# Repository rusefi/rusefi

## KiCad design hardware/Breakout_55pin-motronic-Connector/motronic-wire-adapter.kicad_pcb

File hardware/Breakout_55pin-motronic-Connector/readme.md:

This version of the 55 pin seems to be used by Bosch on BMW/GM ECUs around 1.5.x

See [here](../Breakout_55pin_963063-15-Connector) for another version of connector

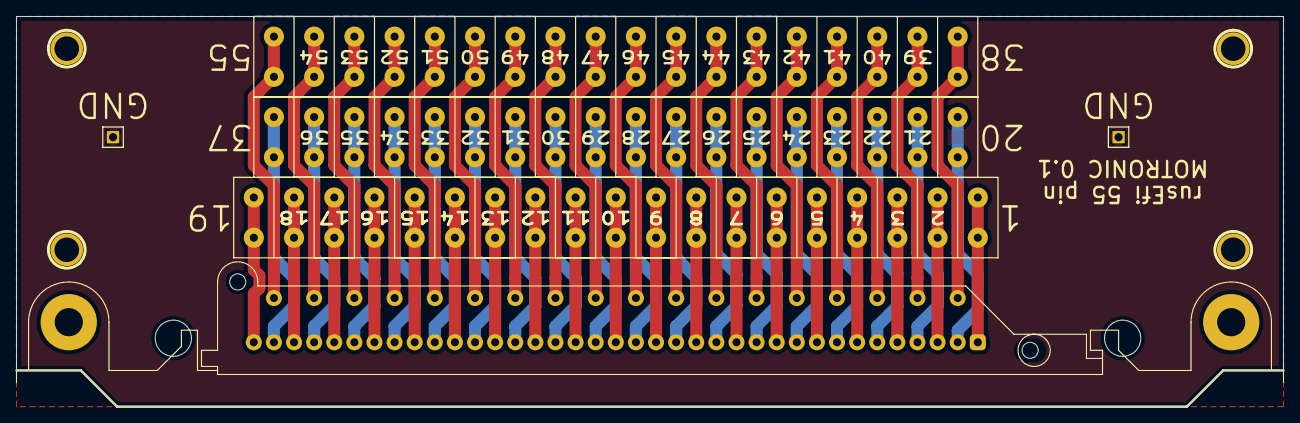
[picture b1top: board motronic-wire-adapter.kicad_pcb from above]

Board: 2 copper layers, 157.5 x 48.5 mm, 10 parts (0 on the bottom side), 56 nets.

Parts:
1PIN, 1PIN#2, 1PIN#3, 1PIN#4: P***; 1pin
P1: MOTRONIC; 55pin_china_bosch_motronic
P2: CONN_19; CON19X5
P3, P4: CONN_18; CON18X5
P5, P6: CONN_1; PIN_ARRAY_1

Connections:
GND: P5.1, P6.1
unnamed: P1.11, P2.11
unnamed: P1.1, P2.1
unnamed: P1.2, P2.2
unnamed: P1.3, P2.3
unnamed: P1.4, P2.4
unnamed: P1.5, P2.5
unnamed: P1.6, P2.6
unnamed: P1.7, P2.7
unnamed: P1.8, P2.8
unnamed: P1.9, P2.9
unnamed: P1.10, P2.10
unnamed: P1.55, P4.18
unnamed: P1.12, P2.12
unnamed: P1.13, P2.13
unnamed: P1.14, P2.14
unnamed: P1.15, P2.15
unnamed: P1.16, P2.16
unnamed: P1.17, P2.17
unnamed: P1.18, P2.18
unnamed: P1.19, P2.19
unnamed: P1.20, P3.1
unnamed: P1.21, P3.2
unnamed: P1.44, P4.7
unnamed: P1.34, P3.15
unnamed: P1.35, P3.16
unnamed: P1.36, P3.17
unnamed: P1.37, P3.18
unnamed: P1.38, P4.1
unnamed: P1.39, P4.2
unnamed: P1.40, P4.3
unnamed: P1.41, P4.4
unnamed: P1.42, P4.5
unnamed: P1.43, P4.6
unnamed: P1.22, P3.3
unnamed: P1.45, P4.8
unnamed: P1.46, P4.9
unnamed: P1.47, P4.10
unnamed: P1.48, P4.11
unnamed: P1.49, P4.12
unnamed: P1.50, P4.13
unnamed: P1.51, P4.14
unnamed: P1.52, P4.15
unnamed: P1.53, P4.16
unnamed: P1.54, P4.17
unnamed: P1.33, P3.14
unnamed: P1.23, P3.4
unnamed: P1.24, P3.5
unnamed: P1.25, P3.6
unnamed: P1.26, P3.7
unnamed: P1.27, P3.8
unnamed: P1.28, P3.9
unnamed: P1.29, P3.10
unnamed: P1.30, P3.11
unnamed: P1.31, P3.12
unnamed: P1.32, P3.13

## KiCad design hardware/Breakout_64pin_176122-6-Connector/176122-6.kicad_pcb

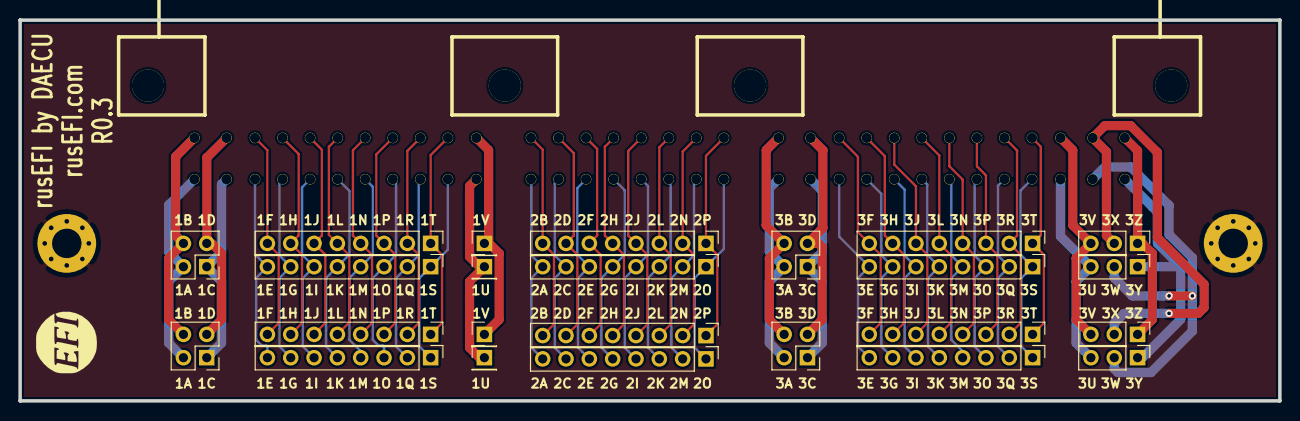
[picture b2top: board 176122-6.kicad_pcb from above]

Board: 2 copper layers, 137.2 x 41.5 mm, 28 parts (0 on the bottom side), 65 nets.

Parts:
G1: LOGO
H1, H2: MountingHole_Pad; MountingHole_3.2mm_M3_Pad_Via
P1, P2, P13, P14: CONN_3; PinHeader_1x03_P2.54mm_Vertical
P3, P4, P42, P43: Conn_01x04_Male; PinHeader_2x02_P2.54mm_Vertical
P7, P8, P19, P20: CONN_1; PinHeader_1x01_P2.54mm_Vertical
P25: 0176122-06; 176122-6
P26, P27, P28, P29, P30, P31, P32, P33, P34, P35, P36, P37: CONN_8; PinHeader_1x08_P2.54mm_Vertical

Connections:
GND: H1.1, H2.1
unnamed: P1.1, P13.1, P25.1
unnamed: P1.2, P13.2, P25.2
unnamed: P1.3, P13.3, P25.3
unnamed: P2.1, P14.1, P25.4
unnamed: P2.2, P14.2, P25.5
unnamed: P2.3, P14.3, P25.6
unnamed: P7.1, P19.1, P25.11
unnamed: P8.1, P20.1, P25.12
unnamed: P3.1, P4.1, P25.7
unnamed: P3.2, P4.2, P25.8
unnamed: P3.3, P4.3, P25.9
unnamed: P3.4, P4.4, P25.10
unnamed: P25.13, P42.1, P43.1
unnamed: P25.14, P42.2, P43.2
unnamed: P25.15, P42.3, P43.3
unnamed: P25.16, P42.4, P43.4
unnamed: P25.17, P26.1, P32.1
unnamed: P25.18, P26.2, P32.2
unnamed: P25.19, P26.3, P32.3
unnamed: P25.20, P26.4, P32.4
unnamed: P25.21, P26.5, P32.5
unnamed: P25.22, P26.6, P32.6
unnamed: P25.23, P26.7, P32.7
unnamed: P25.24, P26.8, P32.8
unnamed: P25.25, P27.1, P33.1
unnamed: P25.26, P27.2, P33.2
unnamed: P25.27, P27.3, P33.3
unnamed: P25.28, P27.4, P33.4
unnamed: P25.29, P27.5, P33.5
unnamed: P25.30, P27.6, P33.6
unnamed: P25.31, P27.7, P33.7
unnamed: P25.32, P27.8, P33.8
unnamed: P25.33, P28.1, P34.1
unnamed: P25.34, P28.2, P34.2
unnamed: P25.35, P28.3, P34.3
unnamed: P25.36, P28.4, P34.4
unnamed: P25.37, P28.5, P34.5
unnamed: P25.38, P28.6, P34.6
unnamed: P25.39, P28.7, P34.7
unnamed: P25.40, P28.8, P34.8
unnamed: P25.41, P29.1, P35.1
unnamed: P25.42, P29.2, P35.2
unnamed: P25.43, P29.3, P35.3
unnamed: P25.44, P29.4, P35.4
unnamed: P25.45, P29.5, P35.5
unnamed: P25.46, P29.6, P35.6
unnamed: P25.47, P29.7, P35.7
unnamed: P25.48, P29.8, P35.8
unnamed: P25.49, P30.1, P36.1
unnamed: P25.50, P30.2, P36.2
unnamed: P25.51, P30.3, P36.3
unnamed: P25.52, P30.4, P36.4
unnamed: P25.53, P30.5, P36.5
unnamed: P25.54, P30.6, P36.6
unnamed: P25.55, P30.7, P36.7
unnamed: P25.56, P30.8, P36.8
unnamed: P25.57, P31.1, P37.1
unnamed: P25.58, P31.2, P37.2
unnamed: P25.59, P31.3, P37.3
unnamed: P25.60, P31.4, P37.4
unnamed: P25.61, P31.5, P37.5
unnamed: P25.62, P31.6, P37.6
unnamed: P25.63, P31.7, P37.7
unnamed: P25.64, P31.8, P37.8

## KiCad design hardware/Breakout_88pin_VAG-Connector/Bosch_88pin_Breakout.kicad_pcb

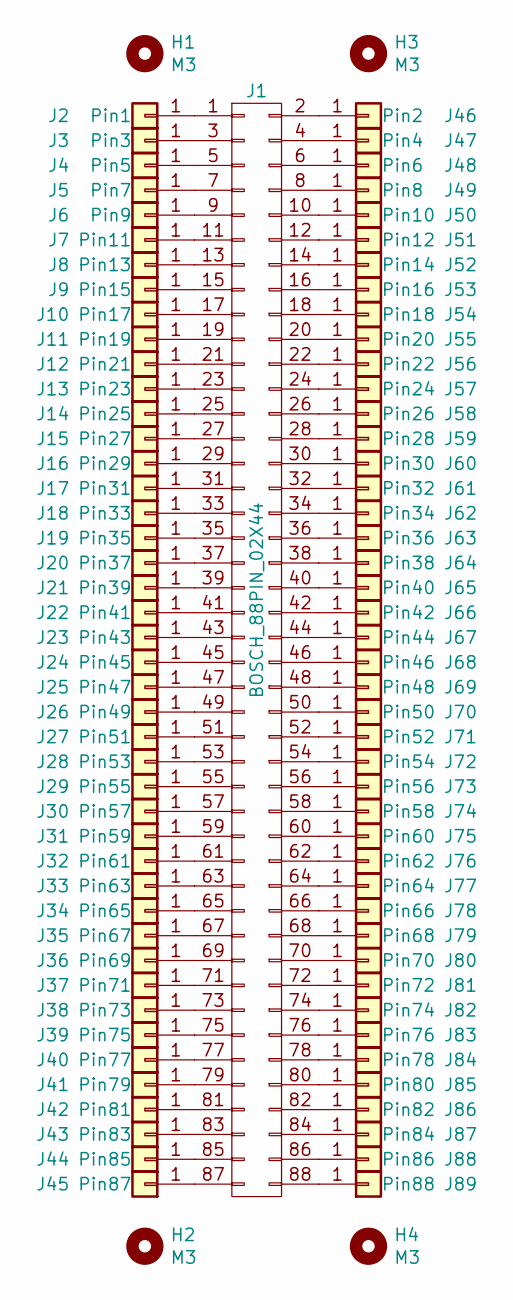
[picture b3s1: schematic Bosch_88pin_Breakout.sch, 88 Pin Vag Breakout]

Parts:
H1, H2, H3, H4: M3; MountingHole_3.2mm_M3_DIN965
J1: BOSCH_88PIN_02X44; BOSCH-88pin
J2: Pin1; TestPoint_Bridge_Pitch2.54mm_Drill1.3mm
J3: Pin3; TestPoint_Bridge_Pitch2.54mm_Drill1.3mm
J4: Pin5; TestPoint_Bridge_Pitch2.54mm_Drill1.3mm
J5: Pin7; TestPoint_Bridge_Pitch2.54mm_Drill1.3mm
J6: Pin9; TestPoint_Bridge_Pitch2.54mm_Drill1.3mm
J7: Pin11; TestPoint_Bridge_Pitch2.54mm_Drill1.3mm
J8: Pin13; TestPoint_Bridge_Pitch2.54mm_Drill1.3mm
J9: Pin15; TestPoint_Bridge_Pitch2.54mm_Drill1.3mm
J10: Pin17; TestPoint_Bridge_Pitch2.54mm_Drill1.3mm
J11: Pin19; TestPoint_Bridge_Pitch2.54mm_Drill1.3mm
J12: Pin21; TestPoint_Bridge_Pitch2.54mm_Drill1.3mm
J13: Pin23; TestPoint_Bridge_Pitch2.54mm_Drill1.3mm
J14: Pin25; TestPoint_Bridge_Pitch2.54mm_Drill1.3mm
J15: Pin27; TestPoint_Bridge_Pitch2.54mm_Drill1.3mm
J16: Pin29; TestPoint_Bridge_Pitch2.54mm_Drill1.3mm
J17: Pin31; TestPoint_Bridge_Pitch2.54mm_Drill1.3mm
J18: Pin33; TestPoint_Bridge_Pitch2.54mm_Drill1.3mm
J19: Pin35; TestPoint_Bridge_Pitch2.54mm_Drill1.3mm
J20: Pin37; TestPoint_Bridge_Pitch2.54mm_Drill1.3mm
J21: Pin39; TestPoint_Bridge_Pitch2.54mm_Drill1.3mm
J22: Pin41; TestPoint_Bridge_Pitch2.54mm_Drill1.3mm
J23: Pin43; TestPoint_Bridge_Pitch2.54mm_Drill1.3mm
J24: Pin45; TestPoint_Bridge_Pitch2.54mm_Drill1.3mm
J25: Pin47; TestPoint_Bridge_Pitch2.54mm_Drill1.3mm
J26: Pin49; TestPoint_Bridge_Pitch2.54mm_Drill1.3mm
J27: Pin51; TestPoint_Bridge_Pitch2.54mm_Drill1.3mm
J28: Pin53; TestPoint_Bridge_Pitch2.54mm_Drill1.3mm
J29: Pin55; TestPoint_Bridge_Pitch2.54mm_Drill1.3mm
J30: Pin57; TestPoint_Bridge_Pitch2.54mm_Drill1.3mm
J31: Pin59; TestPoint_Bridge_Pitch2.54mm_Drill1.3mm
J32: Pin61; TestPoint_Bridge_Pitch2.54mm_Drill1.3mm
J33: Pin63; TestPoint_Bridge_Pitch2.54mm_Drill1.3mm
J34: Pin65; TestPoint_Bridge_Pitch2.54mm_Drill1.3mm
J35: Pin67; TestPoint_Bridge_Pitch2.54mm_Drill1.3mm
J36: Pin69; TestPoint_Bridge_Pitch2.54mm_Drill1.3mm
J37: Pin71; TestPoint_Bridge_Pitch2.54mm_Drill1.3mm
J38: Pin73; TestPoint_Bridge_Pitch2.54mm_Drill1.3mm
J39: Pin75; TestPoint_Bridge_Pitch2.54mm_Drill1.3mm
J40: Pin77; TestPoint_Bridge_Pitch2.54mm_Drill1.3mm
J41: Pin79; TestPoint_Bridge_Pitch2.54mm_Drill1.3mm
J42: Pin81; TestPoint_Bridge_Pitch2.54mm_Drill1.3mm
J43: Pin83; TestPoint_Bridge_Pitch2.54mm_Drill1.3mm
J44: Pin85; TestPoint_Bridge_Pitch2.54mm_Drill1.3mm
J45: Pin87; TestPoint_Bridge_Pitch2.54mm_Drill1.3mm
J46: Pin2; TestPoint_Bridge_Pitch2.54mm_Drill1.3mm
J47: Pin4; TestPoint_Bridge_Pitch2.54mm_Drill1.3mm
J48: Pin6; TestPoint_Bridge_Pitch2.54mm_Drill1.3mm
J49: Pin8; TestPoint_Bridge_Pitch2.54mm_Drill1.3mm
J50: Pin10; TestPoint_Bridge_Pitch2.54mm_Drill1.3mm
J51: Pin12; TestPoint_Bridge_Pitch2.54mm_Drill1.3mm
J52: Pin14; TestPoint_Bridge_Pitch2.54mm_Drill1.3mm
J53: Pin16; TestPoint_Bridge_Pitch2.54mm_Drill1.3mm
J54: Pin18; TestPoint_Bridge_Pitch2.54mm_Drill1.3mm
J55: Pin20; TestPoint_Bridge_Pitch2.54mm_Drill1.3mm
J56: Pin22; TestPoint_Bridge_Pitch2.54mm_Drill1.3mm
J57: Pin24; TestPoint_Bridge_Pitch2.54mm_Drill1.3mm
J58: Pin26; TestPoint_Bridge_Pitch2.54mm_Drill1.3mm
J59: Pin28; TestPoint_Bridge_Pitch2.54mm_Drill1.3mm
J60: Pin30; TestPoint_Bridge_Pitch2.54mm_Drill1.3mm
J61: Pin32; TestPoint_Bridge_Pitch2.54mm_Drill1.3mm
J62: Pin34; TestPoint_Bridge_Pitch2.54mm_Drill1.3mm
J63: Pin36; TestPoint_Bridge_Pitch2.54mm_Drill1.3mm
J64: Pin38; TestPoint_Bridge_Pitch2.54mm_Drill1.3mm
J65: Pin40; TestPoint_Bridge_Pitch2.54mm_Drill1.3mm
J66: Pin42; TestPoint_Bridge_Pitch2.54mm_Drill1.3mm
J67: Pin44; TestPoint_Bridge_Pitch2.54mm_Drill1.3mm
J68: Pin46; TestPoint_Bridge_Pitch2.54mm_Drill1.3mm
J69: Pin48; TestPoint_Bridge_Pitch2.54mm_Drill1.3mm
J70: Pin50; TestPoint_Bridge_Pitch2.54mm_Drill1.3mm
J71: Pin52; TestPoint_Bridge_Pitch2.54mm_Drill1.3mm
J72: Pin54; TestPoint_Bridge_Pitch2.54mm_Drill1.3mm
J73: Pin56; TestPoint_Bridge_Pitch2.54mm_Drill1.3mm
J74: Pin58; TestPoint_Bridge_Pitch2.54mm_Drill1.3mm
J75: Pin60; TestPoint_Bridge_Pitch2.54mm_Drill1.3mm
J76: Pin62; TestPoint_Bridge_Pitch2.54mm_Drill1.3mm
J77: Pin64; TestPoint_Bridge_Pitch2.54mm_Drill1.3mm
J78: Pin66; TestPoint_Bridge_Pitch2.54mm_Drill1.3mm
J79: Pin68; TestPoint_Bridge_Pitch2.54mm_Drill1.3mm
J80: Pin70; TestPoint_Bridge_Pitch2.54mm_Drill1.3mm
J81: Pin72; TestPoint_Bridge_Pitch2.54mm_Drill1.3mm
J82: Pin74; TestPoint_Bridge_Pitch2.54mm_Drill1.3mm
J83: Pin76; TestPoint_Bridge_Pitch2.54mm_Drill1.3mm
J84: Pin78; TestPoint_Bridge_Pitch2.54mm_Drill1.3mm
J85: Pin80; TestPoint_Bridge_Pitch2.54mm_Drill1.3mm
J86: Pin82; TestPoint_Bridge_Pitch2.54mm_Drill1.3mm
J87: Pin84; TestPoint_Bridge_Pitch2.54mm_Drill1.3mm
J88: Pin86; TestPoint_Bridge_Pitch2.54mm_Drill1.3mm
J89: Pin88; TestPoint_Bridge_Pitch2.54mm_Drill1.3mm

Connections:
unnamed: J1.1, J2.1
unnamed: J1.2, J46.1
unnamed: J1.3, J3.1
unnamed: J1.4, J47.1
unnamed: J1.5, J4.1
unnamed: J1.6, J48.1
unnamed: J1.7, J5.1
unnamed: J1.8, J49.1
unnamed: J1.9, J6.1
unnamed: J1.10, J50.1
unnamed: J1.11, J7.1
unnamed: J1.12, J51.1
unnamed: J1.13, J8.1
unnamed: J1.14, J52.1
unnamed: J1.15, J9.1
unnamed: J1.16, J53.1
unnamed: J1.17, J10.1
unnamed: J1.18, J54.1
unnamed: J1.19, J11.1
unnamed: J1.20, J55.1
unnamed: J1.21, J12.1
unnamed: J1.22, J56.1
unnamed: J1.23, J13.1
unnamed: J1.24, J57.1
unnamed: J1.25, J14.1
unnamed: J1.26, J58.1
unnamed: J1.27, J15.1
unnamed: J1.28, J59.1
unnamed: J1.29, J16.1
unnamed: J1.30, J60.1
unnamed: J1.31, J17.1
unnamed: J1.32, J61.1
unnamed: J1.33, J18.1
unnamed: J1.34, J62.1
unnamed: J1.35, J19.1
unnamed: J1.36, J63.1
unnamed: J1.37, J20.1
unnamed: J1.38, J64.1
unnamed: J1.39, J21.1
unnamed: J1.40, J65.1
unnamed: J1.41, J22.1
unnamed: J1.42, J66.1
unnamed: J1.43, J23.1
unnamed: J1.44, J67.1
unnamed: J1.45, J24.1
unnamed: J1.46, J68.1
unnamed: J1.47, J25.1
unnamed: J1.48, J69.1
unnamed: J1.49, J26.1
unnamed: J1.50, J70.1
unnamed: J1.51, J27.1
unnamed: J1.52, J71.1
unnamed: J1.53, J28.1
unnamed: J1.54, J72.1
unnamed: J1.55, J29.1
unnamed: J1.56, J73.1
unnamed: J1.57, J30.1
unnamed: J1.58, J74.1
unnamed: J1.59, J31.1
unnamed: J1.60, J75.1
unnamed: J1.61, J32.1
unnamed: J1.62, J76.1
unnamed: J1.63, J33.1
unnamed: J1.64, J77.1
unnamed: J1.65, J34.1
unnamed: J1.66, J78.1
unnamed: J1.67, J35.1
unnamed: J1.68, J79.1
unnamed: J1.69, J36.1
unnamed: J1.70, J80.1
unnamed: J1.71, J37.1
unnamed: J1.72, J81.1
unnamed: J1.73, J38.1
unnamed: J1.74, J82.1
unnamed: J1.75, J39.1
unnamed: J1.76, J83.1
unnamed: J1.77, J40.1
unnamed: J1.78, J84.1
unnamed: J1.79, J41.1
unnamed: J1.80, J85.1
unnamed: J1.81, J42.1
unnamed: J1.82, J86.1
unnamed: J1.83, J43.1
unnamed: J1.84, J87.1
unnamed: J1.85, J44.1
unnamed: J1.86, J88.1
unnamed: J1.87, J45.1
unnamed: J1.88, J89.1

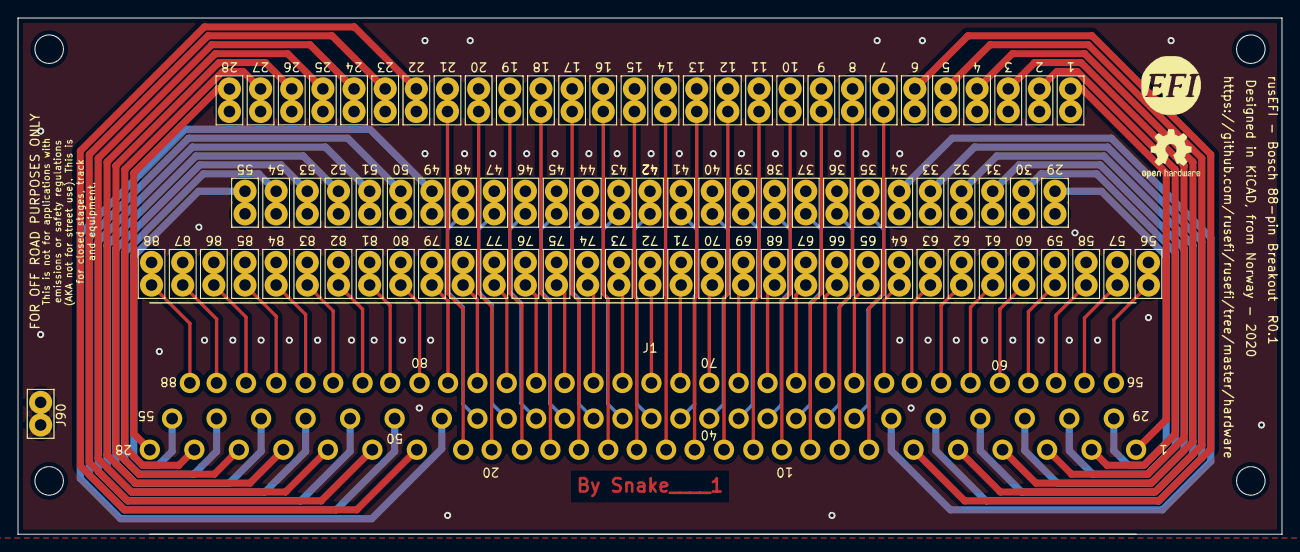
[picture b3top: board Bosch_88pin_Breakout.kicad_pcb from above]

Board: 2 copper layers, 142.0 x 58.0 mm, 97 parts (0 on the bottom side), 88 nets.

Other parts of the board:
G1: LOGO
G2: Disclaimer; Off_Road_Disclaimer
J90: GND; TestPoint_Bridge_Pitch2.54mm_Drill1.3mm
LOGO1: Logo_Open_Hardware_Small; OSHW-Logo2_7.3x6mm_SilkScreen

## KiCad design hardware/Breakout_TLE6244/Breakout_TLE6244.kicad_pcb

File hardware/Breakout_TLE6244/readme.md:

https://rusefi.com/forum/viewtopic.php?f=4&t=577

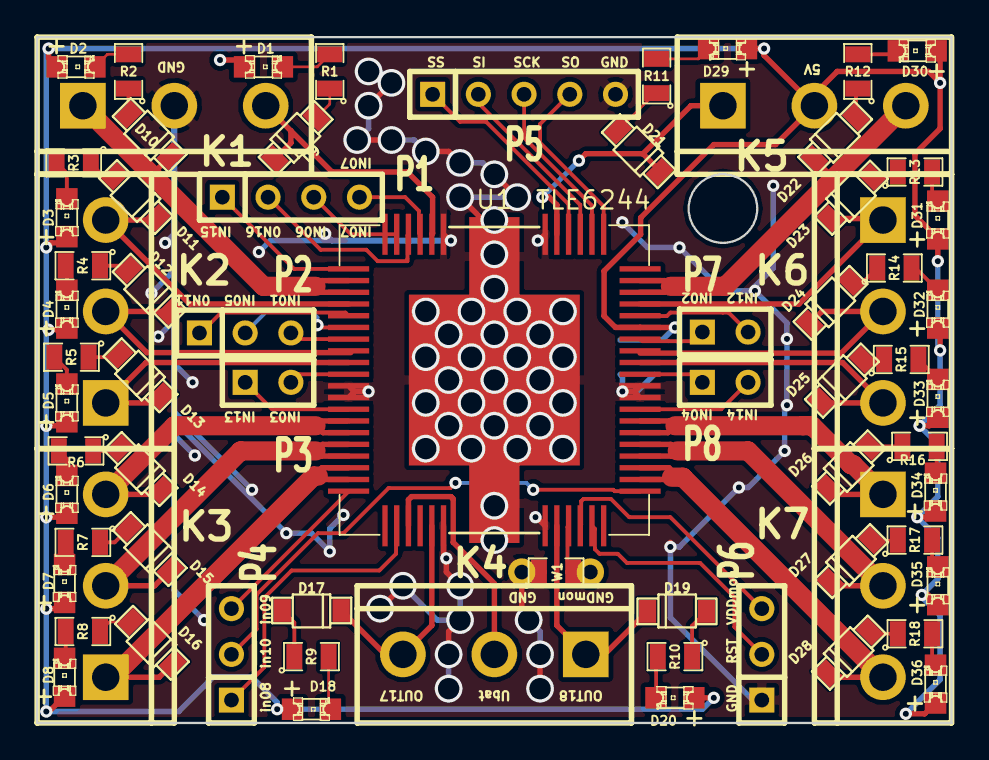
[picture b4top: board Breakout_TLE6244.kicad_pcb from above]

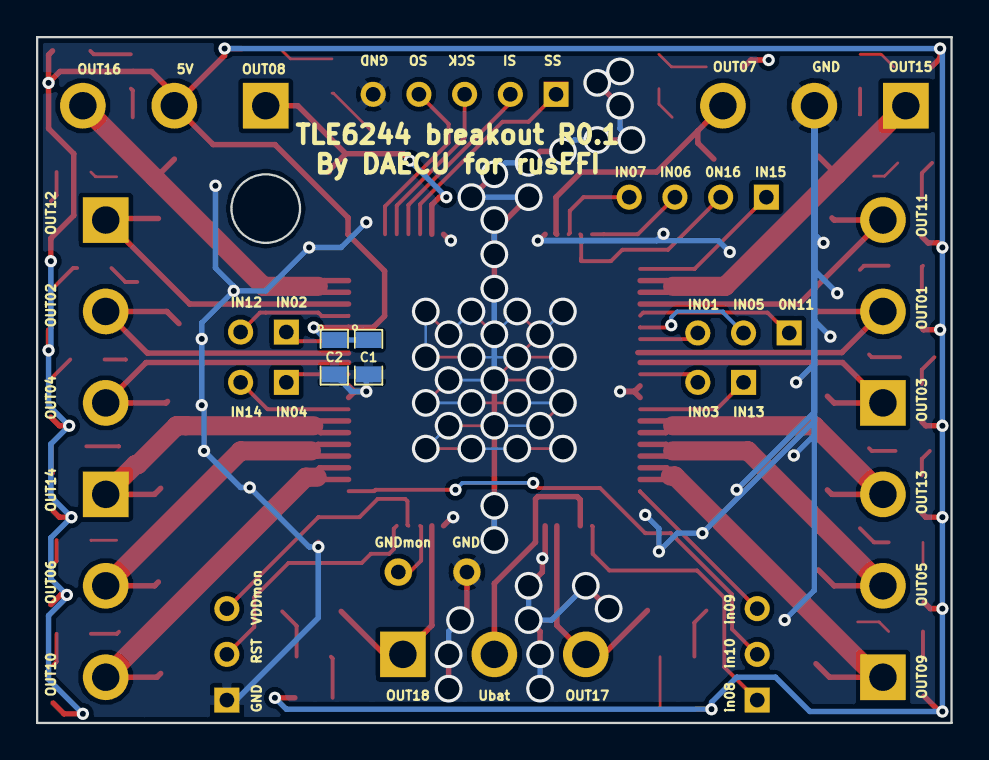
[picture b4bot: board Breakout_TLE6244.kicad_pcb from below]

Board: 4 copper layers, 50.8 x 38.1 mm, 73 parts (2 on the bottom side), 80 nets.

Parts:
C1: 1uF; SM0805
C2: .01uF; SM0805
D1, D2, D3, D4, D5, D6, D7, D8, D18, D20, D29, D30, D31, D32, D33, D34, D35, D36: LED-red; LED-0805_A
D9, D10, D11, D12, D13, D14, D15, D16, D17, D19, D21, D22, D23, D24, D25, D26, D27, D28: DIODE; SOD-123
K1, K2, K3, K4, K5, K6, K7: CONN_3; bornier3
P1: CONN_4; SIL-4
P2, P4, P6: CONN_3; SIL-3
P3, P7, P8: CONN_2; SIL-2
P5: CONN_5; SIL-5
R1, R2, R3, R4, R5, R6, R7, R8, R9, R10, R11, R12, R13, R14, R15, R16, R17, R18: 1K; SM0805
U1: TLE6244; HiQUAD64
W1: TEST; SM0805_jumper

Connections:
/5v: C1.1, C2.1, D1.1, D2.1, D3.1, D4.1, D5.1, D6.1, D7.1, D8.1, D18.1, D20.1, D29.1, D30.1, D31.1, D32.1, D33.1, D34.1, D35.1, D36.1, K5.2, U1.47
/GNDmon: U1.29, W1.2
/RST: P6.2, U1.31
/SCK: P5.3, U1.54
/SI: P5.2, U1.55
/SO: P5.4, U1.53
/SS: P5.1, U1.56
/Ubatt: K4.2, U1.23
/VDDmon: P6.3, U1.30
/in01: P2.3, U1.7
/in02: P7.1, U1.46
/in03: P3.2, U1.10
/in04: P8.1, U1.43
/in05: P2.2, U1.6
/in06: P1.3, U1.63, U1.64
/in07: P1.4, U1.61
/in08: P4.1, U1.22
/in09: P4.3, U1.20
/in10: P4.2, U1.33
/in11: P2.1, U1.5
/in12: P7.2, U1.48
/in13: P3.1, U1.13
/in14: P8.2, U1.40
/in15: P1.1, U1.1
/in16: P1.2, U1.62
/out01: D12.2, K2.2, U1.8
/out02: D24.2, K6.2, U1.45
/out03: D13.2, K2.1, U1.9
/out04: D25.2, K6.3, U1.44
/out05: D15.2, K3.2, U1.16, U1.17
/out06: D27.2, K7.2, U1.36, U1.37
/out07: D9.2, K1.3, U1.60
/out08: D21.2, K5.1, U1.57
/out09: D16.2, K3.1, U1.18, U1.19
/out10: D28.2, K7.3, U1.34, U1.35
/out11: D11.2, K2.3, U1.4
/out12: D23.2, K6.1, U1.49
/out13: D14.2, K3.3, U1.14, U1.15
/out14: D26.2, K7.1, U1.38, U1.39
/out15: D10.2, K1.1, U1.2, U1.3
/out16: D22.2, K5.3, U1.50, U1.51
/out17: D17.2, K4.3, U1.25
/out18: D19.2, K4.1, U1.28
GND: C1.2, C2.2, K1.2, P5.5, P6.1, U1.11, U1.12, U1.26, U1.27, U1.41, U1.42, U1.58, U1.59, U1.slug, W1.1
unnamed: D9.1, R1.1
unnamed: D21.1, R11.1
unnamed: D29.2, R11.2
unnamed: D1.2, R1.2
unnamed: D17.1, R9.1
unnamed: D18.2, R9.2
unnamed: D3.2, R3.2
unnamed: D11.1, R3.1
unnamed: D22.1, R12.1
unnamed: D30.2, R12.2
unnamed: D2.2, R2.2
unnamed: D10.1, R2.1
unnamed: D27.1, R17.1
unnamed: D28.1, R18.1
unnamed: D36.2, R18.2
unnamed: D35.2, R17.2
unnamed: D26.1, R16.1
unnamed: D34.2, R16.2
unnamed: D25.1, R15.1
unnamed: D33.2, R15.2
unnamed: D19.1, R10.1
unnamed: D20.2, R10.2
unnamed: D5.2, R5.2
unnamed: D7.2, R7.2
unnamed: D15.1, R7.1
unnamed: D14.1, R6.1
unnamed: D6.2, R6.2
unnamed: D13.1, R5.1
unnamed: D12.1, R4.1
unnamed: D4.2, R4.2
unnamed: D24.1, R14.1
unnamed: D32.2, R14.2
unnamed: D23.1, R13.1
unnamed: D31.2, R13.2
unnamed: D16.1, R8.1
unnamed: D8.2, R8.2

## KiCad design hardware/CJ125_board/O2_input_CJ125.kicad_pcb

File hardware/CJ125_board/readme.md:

[iBom](https://rusefi.com/docs/ibom/O2_input_CJ125_latest.html)

2019 status: known to work, but documentation is very limited :(

On this board UR and UA do NOT have build-in resistor dividers.

There is an opinion that for open air UA divider is required.

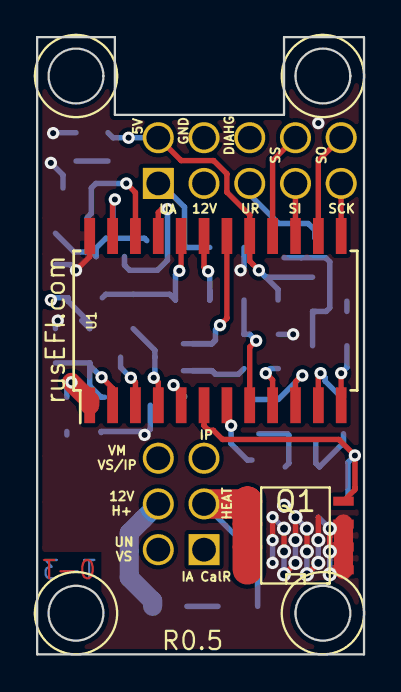
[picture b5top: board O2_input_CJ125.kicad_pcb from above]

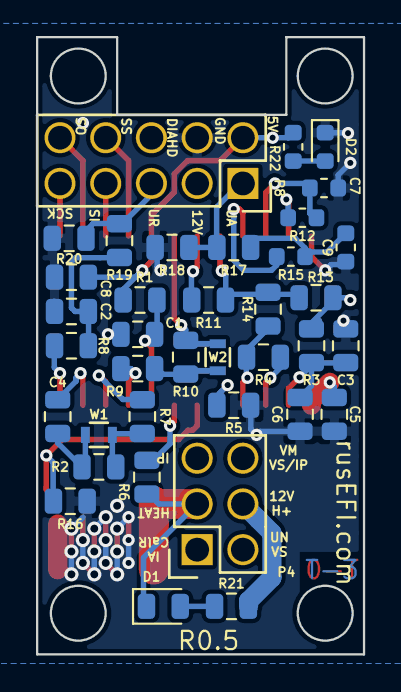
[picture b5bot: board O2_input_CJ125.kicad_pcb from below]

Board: 4 copper layers, 18.2 x 34.3 mm, 39 parts (37 on the bottom side), 35 nets.

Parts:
C1: 1000pF; C_0805_2012Metric
C2, C6, C8: 0.033uF; C_0805_2012Metric
C3: DNP; C_0805_2012Metric
C4: 0.1uF; C_0805_2012Metric
C5: 220pf; C_0805_2012Metric
C7: 0.1uF; C_0603_1608Metric
C9: 0.033uF; C_0603_1608Metric
D1: LED-RED; LED_0805_2012Metric
D2: LED-GRN; LED_0603_1608Metric
P4: CONN_02X03; Socket_Strip_Straight_2x03
P8: CONN_02X05; Socket_Strip_Straight_2x05
Q1: FDS2734; SO8E_ST
R1, R5, R7, R16, R18, R20: 10k; R_0805_2012Metric
R2: 21k6; R_0805_2012Metric
R3: 0R; R_0805_2012Metric
R4: 61.9; R_0805_2012Metric
R6, R17, R19: 6.8k; R_0805_2012Metric
R8: 1k; R_0805_2012Metric
R9: 82.5; R_0805_2012Metric
R10: 220; R_0805_2012Metric
R11: 5.11k; R_0805_2012Metric
R12: 100k; R_0603_1608Metric
R13: 100k; R_0805_2012Metric
R14: 511k; R_0805_2012Metric
R15, R22: 1k; R_0603_1608Metric
R21: 4.7k; R_0805_2012Metric
U1: CJ125; SOIC-24_7.5x15.4mm_Pitch1.27mm
W1, W2: TEST; R_0603

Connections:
/CF: C7.2, R12.1, U1.22
/CJ125_5v: C8.2, P8.2, R1.2, R22.1, U1.17
/CJ125_HEATER: D1.1, P4.3, Q1.2, R6.2
/CJ125_IA: P4.1, R4.2, R14.1, U1.4
/CJ125_IP: P4.5, R4.1, U1.3
/CJ125_SCK: P8.9, U1.13
/CJ125_SI: P8.7, U1.15
/CJ125_SO: P8.10, U1.14
/CJ125_SS: P8.8, U1.16
/CJ125_UA: C9.2, R15.1, R17.2
/CJ125_UN: P4.2, R3.2, R13.1
/CJ125_UR: C2.1, R8.2, R19.2
/CJ125_VM: P4.6, R10.1, U1.18, W2.2
/CM: C4.2, U1.11
/DIAHD: R6.1, U1.7
/DIAHG: P8.6, Q1.1, R16.2, U1.6
/OSZ: R5.2, U1.5
/RF: R12.2, U1.23
/RM: R7.1, U1.10
/RS: R9.2, U1.9
/RST: C1.1, R1.1, U1.8
/UA: R15.2, U1.21
/UN: C3.1, C5.1, R3.1, U1.2
/UP: R11.1, R13.2, R14.2, U1.20
/UR: R8.1, U1.12
/US: R11.2, U1.19
/WO2-12V: C6.2, P4.4, P8.3, R21.2, U1.1
GND: C1.2, C2.2, C3.2, C5.2, C6.1, C7.1, C8.1, C9.1, D2.1, P8.4, Q1.3, R5.1, R16.1, R18.2, R20.2, U1.24
unnamed: C4.1, R2.2, W1.1
unnamed: D1.2, R21.1
unnamed: D2.2, R22.2
unnamed: P8.1, R17.1, R18.1
unnamed: P8.5, R19.1, R20.1
unnamed: R2.1, R7.2, W1.2
unnamed: R9.1, R10.2, W2.1

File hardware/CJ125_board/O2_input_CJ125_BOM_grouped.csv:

Reference, Quantity, Value, Footprint, Datasheet, mfg,mfg#, vend1,vend1#
C1 ,1,1000pF,SM0805,,avx,08052C102KAT2A ,DIGI,478-1339-1-ND
C5 ,1,220pf,SM0805,,avx,08051A221JAT2A,DIGI,478-1286-1-ND
C2 C6 C8 ,3,0.033uF,SM0805,,tdk,CGA4J2C0G1H333J125AA,DIGI,445-6950-1-ND
C3 C4 C7 ,3,0.1uF,SM0805,,avx,08055C104KAT2A,DIGI,478-1395-1-ND
C9 ,1,0.01uF,SM0805,,avx,08055C103JAT2A,DIGI,478-3745-6-ND
P4 ,1,CONN_02X03,Socket_Strips:Socket_Strip_Straight_2x03,,dnp,dnp,dnp,dnp
P8 ,1,CONN_02X05,Socket_Strips:Socket_Strip_Straight_2x05,,dnp,dnp,dnp,dnp
Q1 ,1,FDS2734,SO8E_ST,,ST,VNS14NV04,DIGI,497-11123-1-ND
R10 ,1,117.5,SM0805,,Panasonic,ERJ-6ENF1180V,DIGI,P118CCT-ND
R11 ,1,4.7k,SM0805,,vishay,CRCW08054K70FKEA,DIGI,541-4.70KCCT-ND
R12 R13 ,2,100k,SM0805,,vishay,CRCW0805100KFKEA,DIGI,541-100KCCT-ND
R14 ,1,470k,SM0805,,vishay,CRCW0805470KFKEA,DIGI,541-470KCCT-ND
R15 R8 ,2,1k,SM0805,,Panasonic,ERA-6AEB102V,DIGI,P1.0KDACT-ND
R2 ,1,21k6,SM0805,,vishay,CRCW080521K5FKEA,DIGI,541-21.5KCCT-ND
R3 ,1,160,SM0805,,vishay,CRCW080561R9FKEA,DIGI,541-61.9CCT-ND
R4 ,1,61.9,SM0805,,vishay,CRCW080561R9FKEA,DIGI,541-61.9CCT-ND
R1 R16 R5 R7 ,4,10k,SM0805,,BOURNS,CR0805-FX-1002ELF,DIGI,CR0805-FX-1002ELFCT-ND
R6 ,1,6.8k,SM0805,,vishay,CRCW08056K80FKEA,DIGI,541-6.80KCCT-ND
R9 ,1,82.5,SM0805,,vishay,CRCW080582R5FKEA,DIGI,541-82.5CCT-ND
U1 ,1,CJ125,SOIC-24_7.5x15.4mm_Pitch1.27mm,,bosh,CJ125-1267379259,future,1267379259
W1 W2 ,2,TEST,R_0603,,dnp,dnp,dnp,dnp

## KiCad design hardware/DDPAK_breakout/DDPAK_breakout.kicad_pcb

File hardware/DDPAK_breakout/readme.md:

https://rusefi.com/forum/viewtopic.php?f=4&t=286

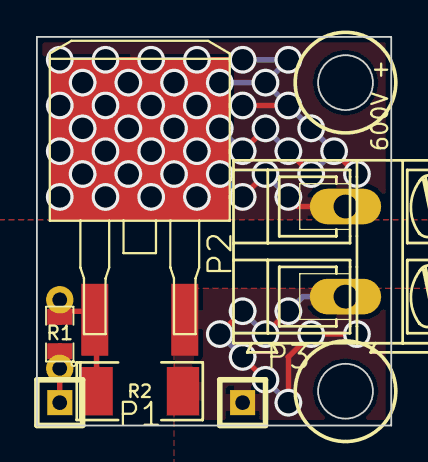
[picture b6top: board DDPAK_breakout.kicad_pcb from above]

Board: 2 copper layers, 19.7 x 21.6 mm, 6 parts (0 on the bottom side), 4 nets.

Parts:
P1, P3: CONN_1; SIL-1
P2: CONN_2; AK300-2
Q1: IRGS14C40L; m-pad-2.1-TO-263AB
R1: 1K; SM0805_jumper
R2: 100K; SM2010

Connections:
/GND: P2.2, P3.1, Q1.3, R2.2
/HV: P2.1, Q1.2
/SIG: P1.1, R1.1
/SIG2: Q1.1, R1.2, R2.1
